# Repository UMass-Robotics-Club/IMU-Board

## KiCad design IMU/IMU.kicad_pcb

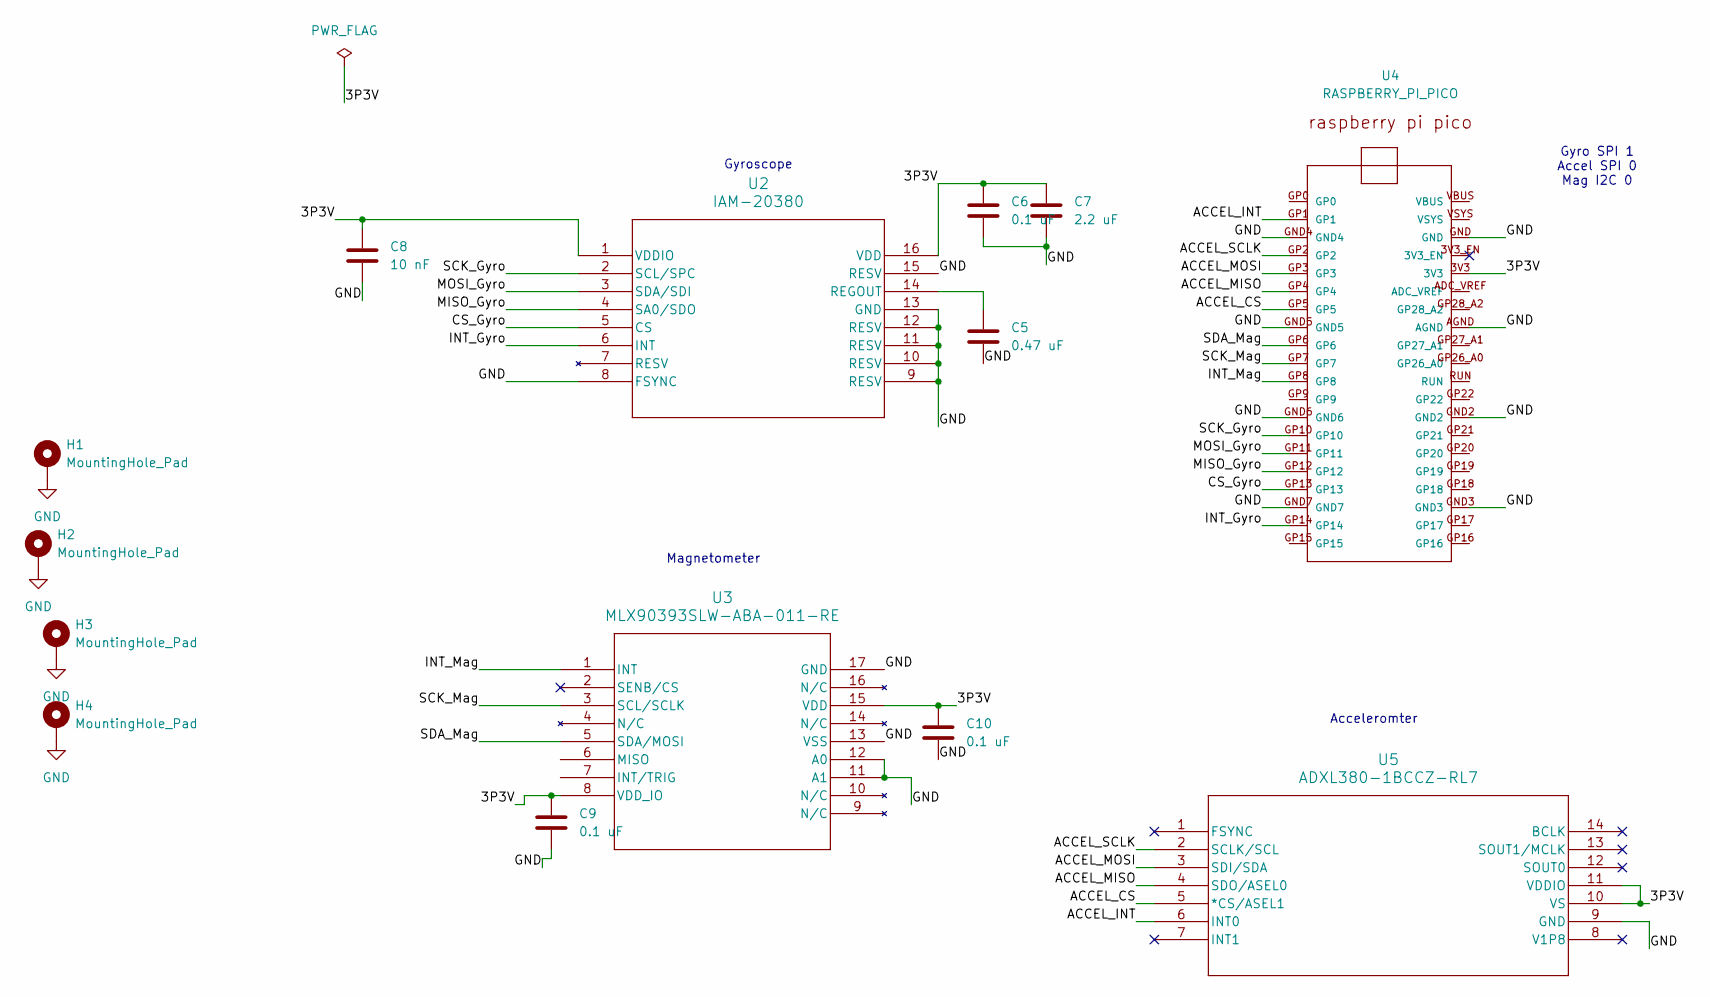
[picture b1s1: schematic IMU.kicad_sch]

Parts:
C5: 0.47 uF; C_0603_1608Metric
C6, C9, C10: 0.1 uF; C_0603_1608Metric
C7: 2.2 uF; C_0603_1608Metric
C8: 10 nF; C_0603_1608Metric
H1, H2, H3, H4: MountingHole_Pad; MountingHole_3.2mm_M3_DIN965_Pad
U2: IAM-20380; IAM-20380_IVS
U3: MLX90393SLW-ABA-011-RE; QFN-16_MLX90393_MEL
U4: RASPBERRY_PI_PICO
U5: ADXL380-1BCCZ-RL7; ADXL380

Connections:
/3P3V: C6.1, C7.1, C8.1, C9.1, C10.1, U2.1 (VDDIO), U2.16 (VDD), U3.8 (VDD_IO), U3.15 (VDD), U4.3V3, U5.10 (VS), U5.11 (VDDIO)
/ACCEL_CS: U4.GP5, U5.5 (*CS/ASEL1)
/ACCEL_INT: U4.GP1, U5.6 (INT0)
/ACCEL_MISO: U4.GP4, U5.4 (SDO/ASEL0)
/ACCEL_MOSI: U4.GP3, U5.3 (SDI/SDA)
/ACCEL_SCLK: U4.GP2, U5.2 (SCLK/SCL)
/CS_Gyro: U2.5 (CS), U4.GP13
/INT_Gyro: U2.6 (INT), U4.GP14
/INT_Mag: U3.1 (INT), U4.GP8
/MISO_Gyro: U2.4 (SA0/SDO), U4.GP12
/MOSI_Gyro: U2.3 (SDA/SDI), U4.GP11
/SCK_Gyro: U2.2 (SCL/SPC), U4.GP10
/SCK_Mag: U3.3 (SCL/SCLK), U4.GP7
/SDA_Mag: U3.5 (SDA/MOSI), U4.GP6
GND: C5.2, C6.2, C7.2, C8.2, C9.2, C10.2, H1.1, H2.1, H3.1, H4.1, U2.8 (FSYNC), U2.9 (RESV), U2.10 (RESV), U2.11 (RESV), U2.12 (RESV), U2.13 (GND), U2.15 (RESV), U3.11 (A1), U3.12 (A0), U3.13 (VSS), U3.17 (GND), U4.AGND, U4.GND, U4.GND2, U4.GND3, U4.GND4, U4.GND5, U4.GND6, U4.GND7, U5.9 (GND)
unnamed: C5.1, U2.14 (REGOUT)

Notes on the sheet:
Acceleromter
Magnetometer
Gyroscope
Gyro SPI 1 Accel SPI 0 Mag I2C 0

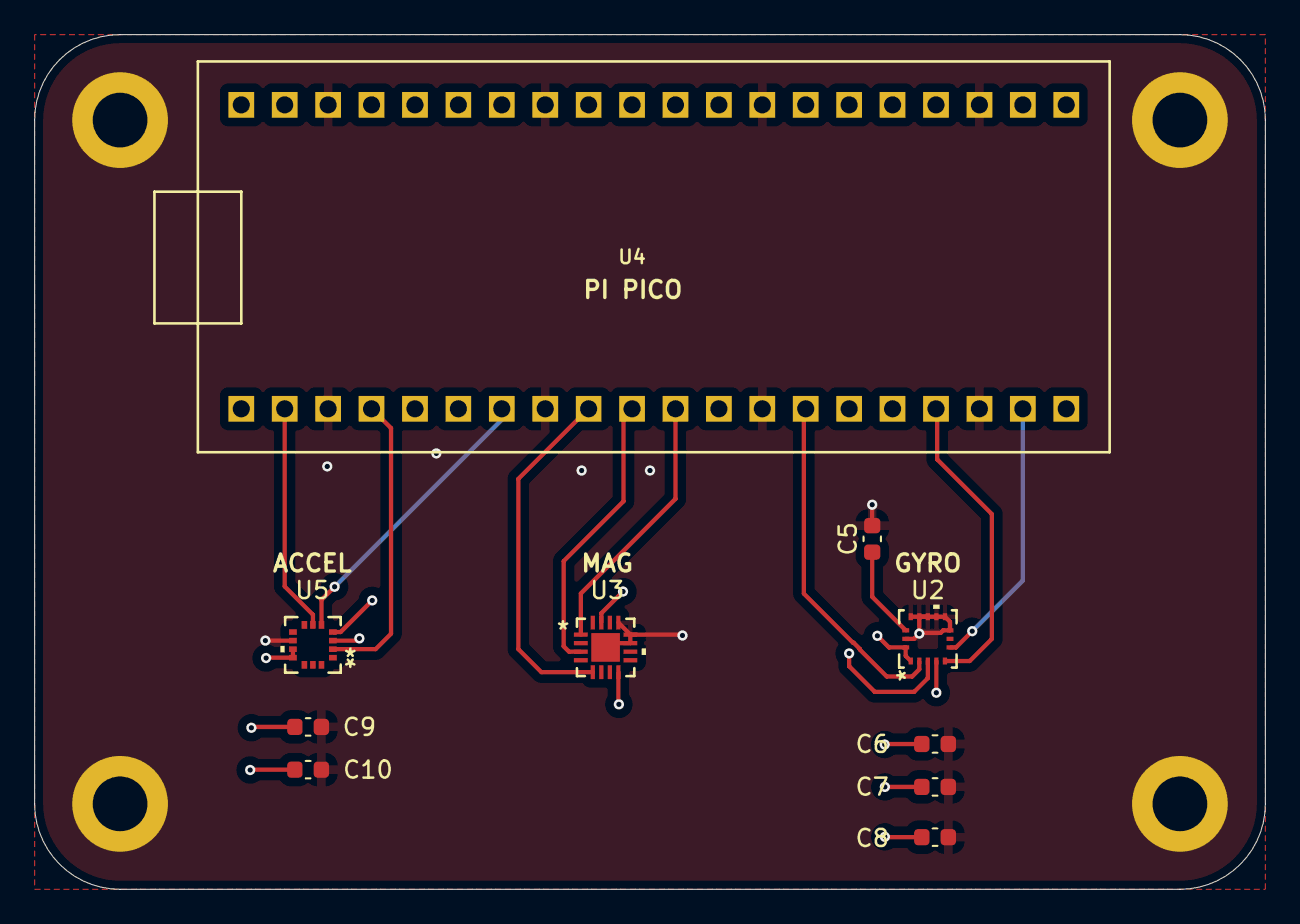
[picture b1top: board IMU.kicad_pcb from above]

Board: 4 copper layers, 72.0 x 50.0 mm, 14 parts (0 on the bottom side), 16 nets.

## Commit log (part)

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2025-10-20 initial commit
    added kicad project
2025-10-23 Added Gyro and Teensy libraries
2025-11-04 Library Changes
    Reorganized parts library structure and fixed file references.
    Added and linked symbols and footprints for all of the non-passive parts. (I haven't yet linked the 3d models to the footprints).
2025-11-06 Finished Schematic!!!
2025-11-06 Ground is important!
2025-11-11 Some layout changes
    Added filled zomes, linked 3d models, added board edge cuts and mounting holes (still need to add filled zone exclusions around the mounting holes to prevent shorts, though I will probably just reduc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
2025-11-15 Update IMU.kicad_sch
    Added a bunch of zero-ohm resistors to the digital pins in case we need to route overboard wires.
    Also added some testpoints for 3.3 and 0 V
2025-11-18 initial imu code
2025-11-18 add angle derivation
2025-11-18 added mag data code
2025-12-02 Some minor Layout changes
2025-12-09 Added dma support
    Switched to pico and added support to dma to run spi and adc in parallel
2026-03-31 fixed board size
2026-03-31 fixed drc
2026-03-31 Final Final Final Changes
    Renamed accel SPI nets for clarity. Changed one of the internal planes to a power plane for 3P3V and removed 3P3V traces. Adjusted design constraints to eliminate DRC warnings/errors.
